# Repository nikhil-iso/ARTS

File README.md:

# ARTS - Amateur Rocketry Telemetry System

ARTS is my flight computer project for logging rocket flight data. The first goal is not to build the whole final flight program at once. The goal is to test each soldered part of the perf board one at a time, make sure the wiring works, and then combine the working pieces later.

The main controller is a Teensy 4.1. Most of the small tests are kept in separate PlatformIO projects under:

```text
flight_computer/testing
```

This keeps the test code away from the main flight computer code.

## Current Hardware Pins

| Part | Teensy Pin / Bus | Notes |
| --- | --- | --- |
| I2C SDA | 18 | Shared by TMP102, KX134, BMP280, and MPU6050 |
| I2C SCL | 19 | Shared I2C clock |
| Buzzer | 5 | Uses `tone()` |
| GPS TX | 0 / RX1 | GPS transmits into Teensy receive |
| GPS RX | 1 / TX1 | Teensy transmits config commands to GPS |
| TMP102 | I2C address `0x48` | Found by scanner |
| KX134 | I2C address `0x1F` | Found by scanner |
| BMP280 | I2C address `0x77` | Confirmed from module |
| MPU6050 | I2C address `0x68` | Used for GPS antenna orientation testing |

For UART wiring, TX and RX are crossed:

```text
GPS TX -> Teensy pin 0 RX1
GPS RX -> Teensy pin 1 TX1
```

## How To Run A Test

Each test is its own PlatformIO project. Open the specific test folder in PlatformIO, upload it to the Teensy, then open the Serial Monitor at `115200` baud unless the test says otherwise.

Example:

```text
flight_computer/testing/i2c_scanner
```

Open that folder, not just the root repo, if PlatformIO is having trouble finding the right `platformio.ini`.

## Test Folder List

### Buzzer Test

Folder:

```text
flight_computer/testing/buzzer_test
```

This checks that the Teensy can drive the buzzer on pin 5.

Expected result:

- one beep at startup
- one beep every 2 seconds
- Serial Monitor prints matching beep messages

### I2C Scanner

Folder:

```text
flight_computer/testing/i2c_scanner
```

This scans the I2C bus and prints all detected devices.

Expected devices so far:

```text
0x1F  KX134/KX13X
0x48  TMP102
0x77  BMP280
0x68  MPU6050, when connected
```

If a device is missing, check 3.3 V, GND, SDA pin 18, SCL pin 19, and the solder joints.

### GPS Test

Folder:

```text
flight_computer/testing/gps_test
```

This checks the Adafruit GPS on `Serial1`.

Expected result:

- raw NMEA lines print in Serial Monitor
- summary lines show fix status, satellite count, UTC time, and position once it gets a fix
- buzzer beeps when a GPS fix is found

No-fix output is still useful. If NMEA lines are printing, the GPS is talking to the Teensy. A fix can take a few minutes, especially indoors.

### TMP102 Test

Folder:

```text
flight_computer/testing/tmp102_test
```

This reads the TMP102 temperature sensor at `0x48`.

Expected result:

- Serial Monitor prints temperature in Celsius and Fahrenheit once per second

### BMP280 Test

Folder:

```text
flight_computer/testing/bmp280_test
```

This reads the BMP280 at `0x77`.

Expected result:

- temperature in Celsius
- pressure in Pascals
- approximate altitude in meters

The altitude is only approximate because it depends on the sea level pressure value used in the code.

### KX134 Test

Folder:

```text
flight_computer/testing/kx134_test
```

This reads the KX134 accelerometer.

Expected result:

- X, Y, and Z acceleration in g
- total acceleration in g

When the board is sitting still, total acceleration should be around 1 g.

### MPU6050 Test

Folder:

```text
flight_computer/testing/mpu6050_test
```

This checks the MPU6050 accelerometer and gyro on the I2C bus.

Expected result:

- `WHO_AM_I` prints as `0x68`
- acceleration prints in g
- gyro rates print in degrees per second
- basic pitch and roll print in degrees

If the board is sitting still, the gyro values should be close to 0 deg/s.

### MPU6050 Visualizer

Folder:

```text
flight_computer/testing/mpu6050_visualizer
```

This streams pitch, roll, and yaw over USB Serial and uses Python to draw a simple 3D rocket orientation view.

Run after uploading the firmware:

```powershell
pip install pyserial matplotlib numpy
python tools\visualize_orientation.py --port COM5
```

Replace `COM5` with the Teensy serial port. Keep the rocket still during startup because the firmware calibrates the gyro first.

The red line in the plot is the rocket body/nose direction. The visualizer assumes the rocket nose is along the sensor's local `+Y` direction. Yaw will drift over time because the MPU6050 does not have a magnetometer.

## GPS Antenna Orientation Test

Folder:

```text
flight_computer/testing/gps_orientation_test
```

This test is for checking which antenna angles give the best GPS signal. It uses:

- Adafruit GPS for satellite data
- MPU6050 for pitch and roll
- USB Serial to stream CSV data to the computer
- Python to save the CSV and make a hotspot plot

The test does not write to the SD card. The computer records the data instead.

### GPS Orientation Wiring

```text
GPS TX -> Teensy pin 0 RX1
GPS RX -> Teensy pin 1 TX1
MPU6050 SDA -> Teensy pin 18 SDA
MPU6050 SCL -> Teensy pin 19 SCL
All grounds connected
```

MPU6050 default address is `0x68`. If AD0 is tied high, it may be `0x69`.

### What GSV Means

The GPS normally sends basic NMEA sentences like RMC and GGA. For the orientation test, the code enables extra GSV sentences.

GSV gives satellite signal strength values, usually called SNR. This is useful because fix/no-fix alone is too basic for testing antenna orientation. SNR gives a better idea of which angle is actually stronger.

The downside is that the GPS sends more serial text. For a 1 Hz test this is fine.

### Running The Orientation Logger

Upload the firmware from:

```text
flight_computer/testing/gps_orientation_test
```

Install Python packages if needed:

```powershell
pip install pyserial matplotlib
```

Then run the collector from the test folder:

```powershell
python tools\collect_and_plot.py --port COM5 --seconds 600
```

Replace `COM5` with the Teensy serial port.

Hold each orientation for about 60 seconds. For example, test flat, tilted left, tilted right, tilted forward, and tilted backward. The script saves:

```text
gps_orientation_data.csv
gps_orientation_hotspot.png
```

The default plot uses `avg_snr`, which is the average GPS signal strength from visible satellites. Higher is better.

Other metrics can also be plotted:

```powershell
python tools\collect_and_plot.py --port COM5 --seconds 600 --metric best_snr
python tools\collect_and_plot.py --port COM5 --seconds 600 --metric sats_visible
python tools\collect_and_plot.py --port COM5 --seconds 600 --metric sats_used
python tools\collect_and_plot.py --port COM5 --seconds 600 --metric hdop
```

For HDOP, lower is better. For SNR and satellite counts, higher is better.

## Suggested Bring-Up Order

1. Run `buzzer_test`.
2. Run `i2c_scanner`.
3. Run `tmp102_test`.
4. Run `bmp280_test`.
5. Run `kx134_test`.
6. Run `mpu6050_test`.
7. Run `mpu6050_visualizer`.
8. Run `gps_test`.
9. Add the MPU6050 and run `gps_orientation_test`.

This order keeps the debugging simple. If something fails, there are fewer parts involved.

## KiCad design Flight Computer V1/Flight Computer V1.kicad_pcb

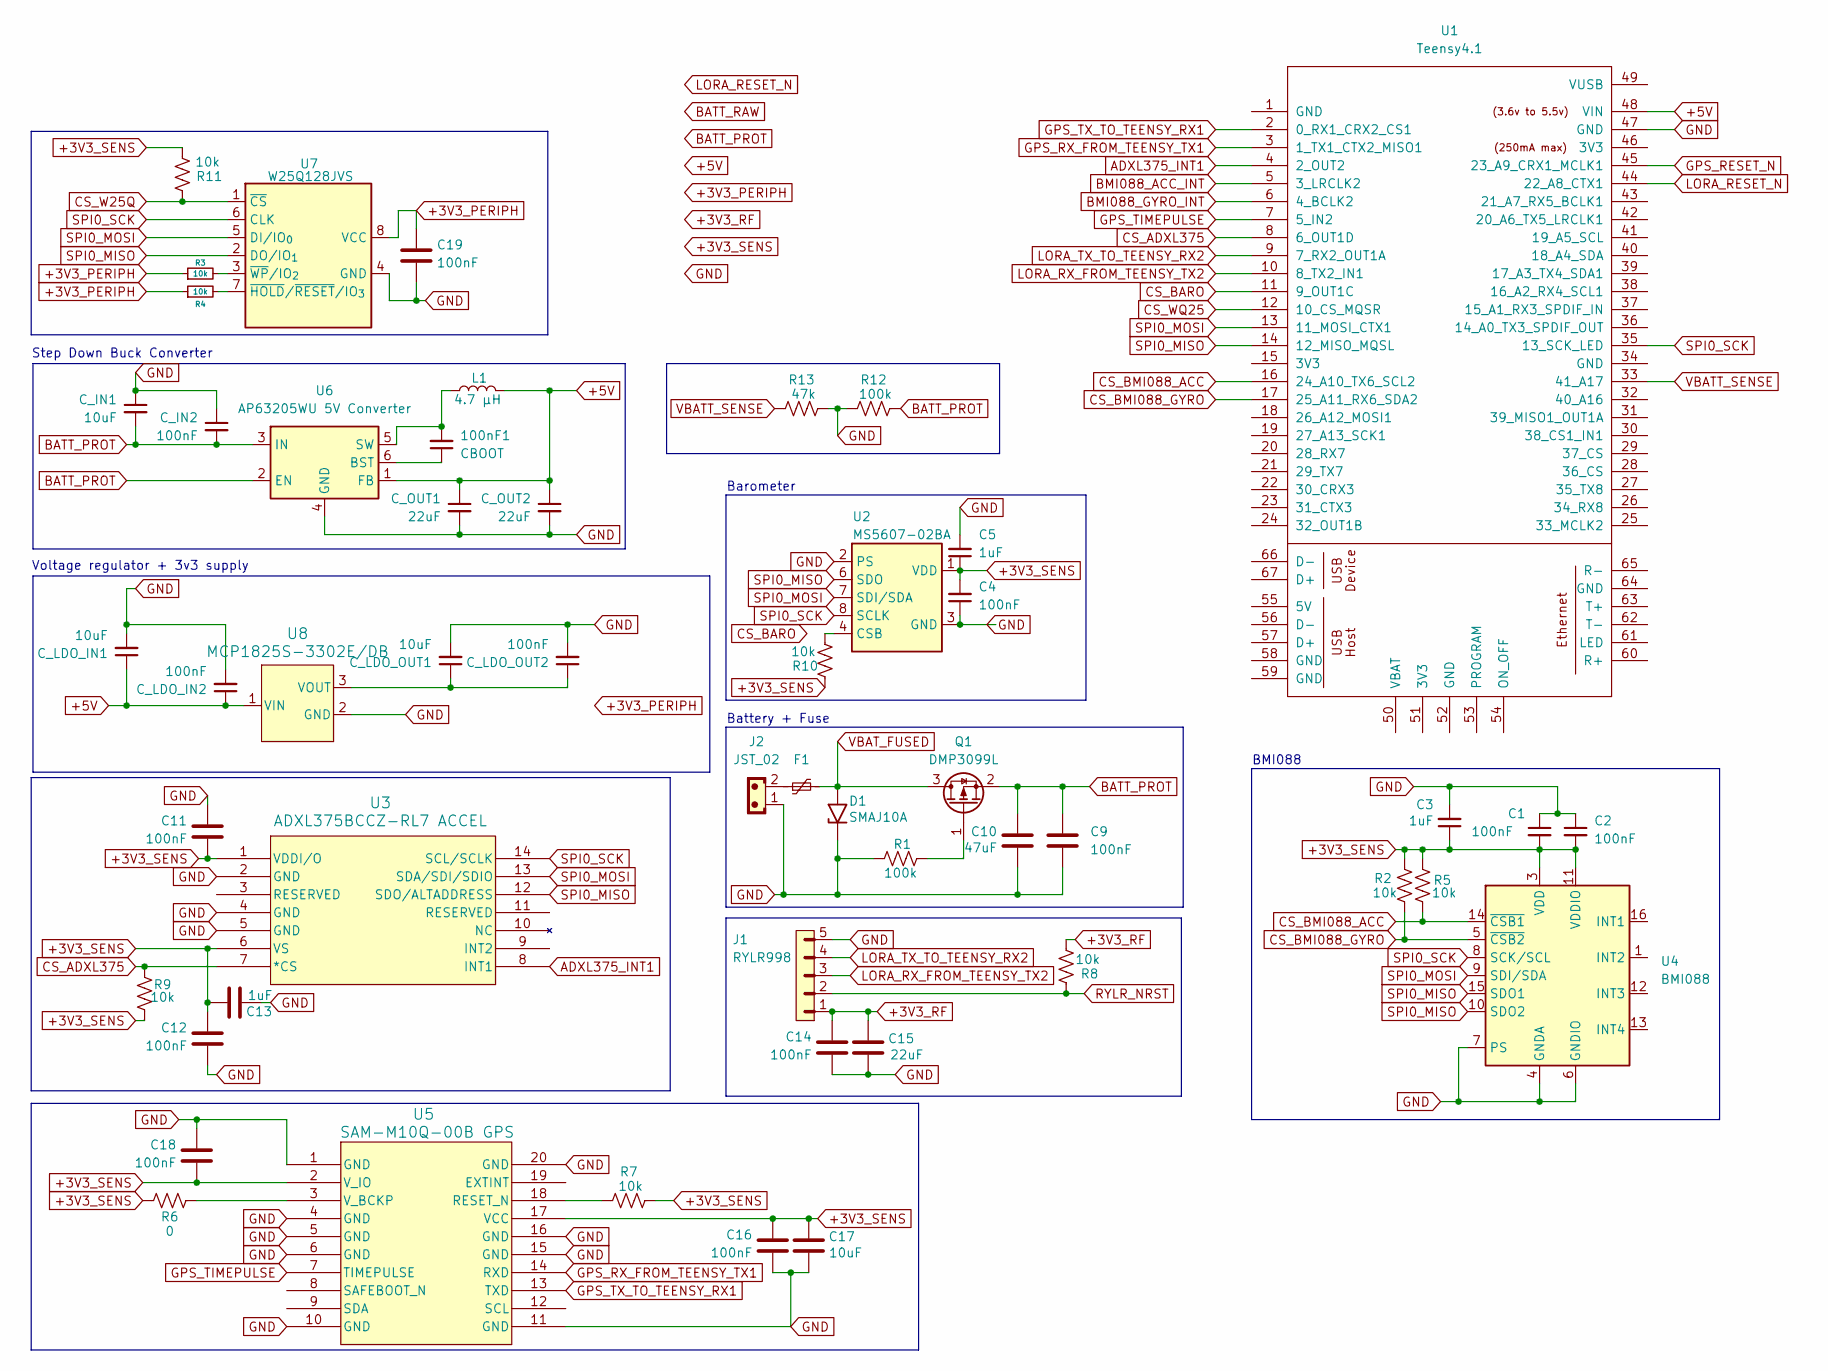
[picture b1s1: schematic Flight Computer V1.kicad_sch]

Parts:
100nF1: CBOOT; C_0805_2012Metric
C1, C2, C4, C9, C11, C12, C14, C16, C18, C19: 100nF; C_0805_2012Metric
C3, C5, C13: 1uF; C_0805_2012Metric
C10: 47uF; C_0805_2012Metric
C15: 22uF; C_0805_2012Metric
C17: 10uF; C_0805_2012Metric
C_IN1: 10uF; C_0805_2012Metric
C_IN2: 100nF; R_0805_2012Metric
C_LDO_IN1: 10uF; C_0805_2012Metric
C_LDO_IN2: 100nF; C_0805_2012Metric
C_LDO_OUT1: 10uF; C_0805_2012Metric
C_LDO_OUT2: 100nF; C_0805_2012Metric
C_OUT1, C_OUT2: 22uF; C_0805_2012Metric
D1: SMAJ10A; D_SMA
F1: Polyfuse_Small; Fuse_1812_4532Metric
J1: RYLR998; PinHeader_1x05_P2.54mm_Vertical
J2: JST_02; JST_EH_B2B-EH-A_1x02_P2.50mm_Vertical
L1: 4.7 µH; L_Bourns-SRN6028
Q1: DMP3099L; SOT-23
R1, R12: 100k; R_01005_0402Metric
R2, R5, R7, R8, R9, R10: 10k; R_01005_0402Metric
R3, R4, R11: 10k; R_0805_2012Metric
R6: 0; R_01005_0402Metric
R13: 47k; R_01005_0402Metric
U1: Teensy4.1; Teensy41
U2: MS5607-02BA; LGA-8_3x5mm_P1.25mm
U3: ADXL375BCCZ-RL7 ACCEL; LGA_CC-14-1_ADI
U4: BMI088; Bosch_LGA-16_4.5x3mm_P0.5mm_LayoutBorder7x1y_ClockwisePinNu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
U5: SAM-M10Q-00B GPS; SAM-M10Q_UBL
U6: AP63205WU 5V Converter; TSOT-23-6
U7: W25Q128JVS; WSON_128JVPIQ_WIN
U8: MCP1825S-3302E/DB; SOT-223_3MC_MCH

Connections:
+3V3_PERIPH: C19.1, R3.1, R4.1, U7.8 (VCC)
+3V3_RF: C14.1, C15.2, J1.1, R8.1
+3V3_SENS: C1.2, C2.2, C3.1, C4.2, C5.1, C11.2, C12.1, C13.1, C16.1, C17.2, C18.2, R2.1, R5.2, R6.2, R7.1, R9.2, R10.2, R11.1, U2.1 (VDD), U3.1 (VDDI/O), U3.6 (VS), U4.3 (VDD), U4.11 (VDDIO), U5.2 (V_IO), U5.17 (VCC)
+5V: C_LDO_IN1.1, C_LDO_IN2.1, C_OUT1.1, C_OUT2.1, L1.2, U1.48 (VIN), U6.1 (FB), U8.1 (VIN)
ADXL375_INT1: U1.4 (2_OUT2), U3.8 (INT1)
BATT_PROT: C9.1, C10.1, C_IN1.2, C_IN2.2, Q1.2 (S), R12.1, U6.2 (EN), U6.3 (IN)
BMI088_ACC_INT: U1.5 (3_LRCLK2)
BMI088_GYRO_INT: U1.6 (4_BCLK2)
CS_ADXL375: R9.1, U1.8 (6_OUT1D), U3.7 (*CS)
CS_BARO: U1.11 (9_OUT1C)
CS_BMI088_ACC: R5.1, U1.16 (24_A10_TX6_SCL2), U4.14 (~CSB1)
CS_BMI088_GYRO: R2.2, U1.17 (25_A11_RX6_SDA2), U4.5 (~CSB2)
CS_W25Q: R11.2, U7.1 (~CS)
CS_WQ25: U1.12 (10_CS_MQSR)
GND: C1.1, C2.1, C3.2, C4.1, C5.2, C9.2, C10.2, C11.1, C12.2, C13.2, C14.2, C15.1, C16.2, C17.1, C18.1, C19.2, C_IN1.1, C_IN2.1, C_LDO_IN1.2, C_LDO_IN2.2, C_LDO_OUT1.2, C_LDO_OUT2.2, C_OUT1.2, C_OUT2.2, D1.1 (A1), J1.5, J2.1, R1.2, R12.2, R13.1, U1.47 (GND), U2.2 (PS), U2.3 (GND), U3.2 (GND), U3.4 (GND), U3.5 (GND), U4.2 (GNDA), U4.4 (GNDA), U4.6 (GNDIO), U4.7 (PS), U5.1 (GND), U5.4 (GND), U5.5 (GND), U5.6 (GND), U5.10 (GND), U5.11 (GND), U5.15 (GND), U5.16 (GND), U5.20 (GND), U6.4 (GND), U7.4 (GND), U8.2 (GND)
GPS_RESET_N: U1.45 (23_A9_CRX1_MCLK1)
GPS_RX_FROM_TEENSY_TX1: U1.3 (1_TX1_CTX2_MISO1), U5.14 (RXD)
GPS_TIMEPULSE: U1.7 (5_IN2), U5.7 (TIMEPULSE)
GPS_TX_TO_TEENSY_RX1: U1.2 (0_RX1_CRX2_CS1), U5.13 (TXD)
LORA_RESET_N: U1.44 (22_A8_CTX1)
LORA_RX_FROM_TEENSY_TX2: J1.3, U1.10 (8_TX2_IN1)
LORA_TX_TO_TEENSY_RX2: J1.4, U1.9 (7_RX2_OUT1A)
unnamed: F1.1, J2.2
unnamed: Q1.1 (G), R1.1
unnamed: R10.1, U2.4 (CSB), U2.5 (CSB)
unnamed: R7.2, U5.18 (RESET_N)
unnamed: R6.1, U5.3 (V_BCKP)
unnamed: 100nF1.1, U6.6 (BST)
unnamed: 100nF1.2, L1.1, U6.5 (SW)
unnamed: R4.2, U7.7 (~HOLD/~RESET/IO_{3})
unnamed: R3.2, U7.3 (~WP/IO_{2})
unnamed: C_LDO_OUT1.1, C_LDO_OUT2.1, U8.3 (VOUT)
RYLR_NRST: J1.2, R8.2
SPI0_MISO: U1.14 (12_MISO_MQSL), U2.6 (SDO), U3.12 (SDO/ALTADDRESS), U4.10 (SDO2), U4.15 (SDO1), U7.2 (DO/IO_{1})
SPI0_MOSI: U1.13 (11_MOSI_CTX1), U2.7 (SDI/SDA), U3.13 (SDA/SDI/SDIO), U4.9 (SDI/SDA), U7.5 (DI/IO_{0})
SPI0_SCK: U1.35 (13_SCK_LED), U2.8 (SCLK), U3.14 (SCL/SCLK), U4.8 (SCK/SCL), U7.6 (CLK)
VBATT_SENSE: R13.2, U1.33 (41_A17)
VBAT_FUSED: D1.2 (A2), F1.2, Q1.3 (D)

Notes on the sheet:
Step Down Buck Converter
Voltage regulator + 3v3 supply
BMI088
Battery + Fuse
Barometer

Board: 2 copper layers, 52 parts (0 on the bottom side), 32 nets, no tracks yet.

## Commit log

2026-05-21 Added KiCAD files
2026-05-21 Remove obsolete KiCAD files and add project structure files for PlatformIO
2026-05-21 Add user-created library and components for Sparkfun KX134 Breakout Module
    - Created fp-lib-table and sym-lib-table for user-defined libraries.
    - Added backup and symbol files for Sparkfun KX134 Breakout Module.
    - Defined the module footprint with detailed properties and pads.
    - Included necessary properties such as Reference, Value, and Footprint.
    - Ensured compatibility with KiCad version 10.0 and above.
2026-05-22 Add project title to README
2026-05-22 Add MIT License to the project
2026-05-22 Reaname Dir
2026-05-22 Add buzzer test code and PlatformIO configuration
2026-05-23 Refactor code structure for improved readability and maintainability
2026-05-23 Add initial I2C scanner implementation and configuration files
2026-05-25 Add GPS test implementation and configuration files
2026-05-26 Add BMP280 sensor test implementation and configuration files
2026-05-26 Add KX134 accelerometer test implementation and configuration files
2026-05-26 Add TMP102 temperature sensor test implementation and configuration files
2026-06-10 Add MPU6050 test and visualizer implementations with documentation
2026-06-16 Updated Ork
2026-06-17 Updated Flight controller hardware Schematics
2026-06-21 OpenRocket L1 Cert Rocket
